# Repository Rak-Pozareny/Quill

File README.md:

# Quill
A love letter to the classic PDA, but reimagined.

Desktop and phone in one. A clean, all-transparent DORFic design that sits comfortably in your hand. Fully open source, top to bottom. What more could you ask for?
Meet Quill.

> **Status, November 2026.** Both boards are designed, pass every check run before manufacture, and are in
> production at JLCPCB; the compute module has arrived. Nothing has been powered
> on yet: every number on this page is a design value or the result of a check on the design files, not a measurement.

## What Quill is

A pocket computer in the spirit of the classic PDA: a square 4-inch screen above a thumb keyboard, running full desktop
Linux on an eight-core Rockchip RK3588S, with LTE, Wi-Fi 6, two cameras and a 5000 mAh battery. The electronics are two
custom boards: **Board A**, a 6-layer carrier for an Orange Pi CM5 compute module that holds everything except the
keyboard, and **Board B**, which connects a BlackBerry Q20 keyboard over USB.

| | |
|---|---|
| **Compute** | Orange Pi CM5: Rockchip RK3588S (4 x Cortex-A76 + 4 x Cortex-A55), 16 GB LPDDR4X, 32 GB eMMC |
| **Display** | 4.0" 720 x 720 IPS panel (DisplayModule DMKDI0400S0CA, ST7703), 4-lane MIPI DSI, capacitive touch |
| **Keyboard** | BlackBerry Q20 keyboard on Board B (RP2040), USB 2.0 to Board A |
| **Wireless** | Wi-Fi 6 2x2 + Bluetooth 5 (AMPAK AP6275P, PCIe 2.0 + UART); LTE Cat-6 (Quectel EM060K-GL, M.2, USB 3.0); nano-SIM |
| **Cameras** | rear: 4-lane MIPI CSI; front: 2-lane MIPI CSI |
| **Audio** | two I2S class-D amplifiers (MAX98357A) for stereo speakers, PDM MEMS microphone |
| **Ports** | USB-C (USB PD sink up to 12 V, charging and USB 2.0 data), 2 x USB-A behind a USB 2.0 hub, microSD |
| **Power** | 1S Li-ion 5000 mAh; buck-boost charger (BQ25713), fuel gauge (MAX17055), five DC-DC converters; battery path sized for 12 A |
| **Board A** | 95 x 65 mm, 6 layers, 1.2 mm, impedance-controlled; 432 footprints (379 parts placed by machine), 9,637 track segments, 1,841 vias |
| **Board B** | 74 x 53.1 mm, 2 layers, 2.0 mm; 68 parts |

## Architecture

The compute module plugs into Board A through three 100-pin board-to-board connectors (Hirose DF40). High-speed links
are drawn in red: DSI to the display, two CSI links to the cameras, PCIe to the Wi-Fi module, USB 3.0 to the LTE modem,
and USB 2.0 to the hub, the keyboard and the USB-C port.

**Power.** A USB-C PD controller (TPS25751, configured from an EEPROM so that it can boot from a flat battery) negotiates
5, 9 or 12 V and drives a narrow-VDC buck-boost charger. The system rail (VSYS, 3.0-4.5 V) feeds two boost converters
(5.03 V for the compute module, 5.1 V for USB, the keyboard and a camera), two buck-boost converters (3.7 V for the LTE
modem, 3.3 V for Wi-Fi, the hub and the cameras), the backlight driver and the audio amplifiers. With every load at its
maximum at once the battery supplies 33.6 W, 9.8 A at 3.5 V; the connector, protection circuit, battery FET and sense
resistors are all sized for 12 A. Realistic heavy use is about 13.9 W.

## Engineering highlights

### The boards are generated from code

The schematics, footprints, placement and routing are produced by about 16,000 lines of Python and C (`gen/`, `tools/`)
rather than drawn by hand, so every change is reproducible, can be reviewed as a diff, and is checked again on every
build. Board A's routing pipeline (`gen/route_a.py`, about six hours per full run) lays down the power pours and trunks,
routes the differential pairs as coupled lines with their impedance geometry (`gen/route_pairs.py`), fans out every
ground pad, routes the remaining connections with a negotiated-congestion (PathFinder) grid router whose core is written
in C (`gen/groute.c`), and tunes pair lengths with 45-degree bumps (`gen/route_tune.py`). How to run each step:
[docs/BUILDING.md](docs/BUILDING.md).

### Signal integrity on a 6-layer, 1.2 mm board

Layers 2 and 5 are ground planes, so each of the four signal layers has a ground plane next to it as its reference. Trace widths
and gaps come from JLCPCB's impedance calculator for its JLC06121H-3313A stack-up (Polar Si9000 models), and the
outer-layer ground pour keeps 0.30 mm from every controlled trace so that the microstrips behave as calculated:

| Class | Target | Outer layers, width / gap | Inner layers, width / gap | Used for |
|---|---|---|---|---|
| MIPI100 | 100 ohm differential | 0.110 / 0.155 mm | 0.100 / 0.200 mm | display and camera lanes, PCIe reference clocks |
| USB90 | 90 ohm differential | 0.120 / 0.110 mm | 0.100 / 0.110 mm | USB 2.0, USB 3.0 to the modem |
| PCIE85 | 85 ohm differential | 0.130 / 0.100 mm | 0.110 / 0.100 mm | PCIe to the Wi-Fi module |
| SE50 | 50 ohm single-ended | 0.155 mm | 0.125 mm | Wi-Fi antenna feeds, microSD |

Within each of the 31 differential pairs, the two traces match to 0.05 mm or better on 28; the other three are short
stubs, each explained in the decision log. Between lanes, the four display lanes are 55.08-55.22 mm long against a
55.12 mm clock. The camera links are not there yet: two of the rear camera's four lanes are 1.8-2.8 mm (12-20 ps) short
of their clock and the front camera's two lanes 2.8-2.9 mm (20 ps) long, against a +-1.0 mm allowance. Both will be
tested at full lane rate in bring-up ([length report](docs/opi/length_report.md)).

### Verification beyond the design-rule check

KiCad's design-rule check passes with 0 errors and 0 unconnected nets, the schematic and the board match exactly, and
the schematic passes its electrical-rule check. That was not enough, so the project added its own checks:

- **Review by the designer before every submission.** Before each set of Gerbers went to the manufacturer, Rak went
  through the design and the files. That review found, for example, that the part outlines on the silkscreen were drawn
  0.12 mm wide, under JLCPCB's 0.15 mm minimum (KiCad's default, missed by every automated check here; widened to
  0.15 mm for the next revision, D123), and produced a cleaner order package: a Gerber job file giving the fab every
  layer's function and order, and the impedance drawing and table set apart from the board layers with fabrication notes.
- **Engineering review at the manufacturer.** Every order's Gerber, drill, BOM and placement files went through
  JLCPCB's engineering review before production: their CAM engineers check the fabrication files for manufacturability,
  their SMT engineers check parts, land patterns and placement before assembly. Over three submissions of Board A they
  raised three problems (touching track ends, the Wi-Fi module's land pattern, copper too close for V-cut), all fixed and
  listed in the table below; the files now in production passed both reviews, as did Board B's. This is a
  manufacturability review, not a review of the circuit design: an independent design review is still an open item in
  [`REVIEW.md`](REVIEW.md).
- **Gerber-level connectivity** (`tools/gerber_check.py`). KiCad treats copper that merely touches as connected; a
  board house's CAM software does not. The exported Gerbers are read back as geometry and every track and via joint is
  measured the way the fab will see it.
- **Comparison with the manufacturer's production files** (`tools/jlc_prod_check/`). JLCPCB's CAM output for the
  order was parsed and compared with our copper layer by layer (geometric XOR), along with track widths, drill counts
  and any copper they added, before the order was confirmed.
- **Footprint audit** ([`docs/footprint_audit.md`](docs/footprint_audit.md)): each of the 24 footprints generated for
  the project checked against its datasheet drawing, down to which edge or centre each dimension line points to.
- **Parts**: every BOM line checked against JLCPCB's live catalogue (part number, manufacturer number, stock), and
  `tools/datasheets.py` confirms that every non-trivial part has its datasheet in [`datasheets/`](datasheets/README.md).

### What went wrong, and what changed because of it

| Date | What happened | Root cause | Response |
|---|---|---|---|
| 2026-10-30 | JLCPCB's CAM stopped the first order: track ends that only touched | KiCad's checks count touching copper as connected | 395 duplicate tracks removed, 153 joints bridged at full width (D110); the Gerber-level checker added (D116) |
| 2026-10-31 | Found in our own review: the outer ground pour ran 0.09 mm from controlled traces | a pour that close makes a microstrip coplanar, lowering its impedance | 0.30 mm keep-out around every controlled trace (D112) |
| 2026-11-06 | JLCPCB's assembly review: the Wi-Fi module's 50 pads sat 0.56 mm too far in | a datasheet dimension measured between pad centres had been read as between pad edges | footprint corrected, board re-routed (D114); every other footprint audited for the same misreading (D115) |
| 2026-11-10 | The display maker's drawing put pin 1 of both panel cables at the other end | the pin direction had been assumed and was marked UNVERIFIED | connectors mirrored and the whole board routed again (D118) |
| 2026-11-15 | JLCPCB: copper too close to the edge rails for V-cut separation | 0.25 mm edge clearance, fine for routed edges, too small for V-cut | rails joined by mouse-bite tabs instead; 0.4 mm clearance for the next revision (D122) |

### Every decision is written down

[`docs/DECISIONS.md`](docs/DECISIONS.md) records 122 design decisions and 22 answered design questions, each with the
choice, the alternatives and the reason, and the sources behind it. Anything not confirmed from a primary source (a
datasheet, a drawing, a measurement) is marked **UNVERIFIED** until it is.

<p align="center"><sub>Left: Board A, bottom side (LTE modem, Wi-Fi module, power stages). Right: Board B, the keyboard board.</sub></p>

## Repository

| Path | Contents |
|---|---|
| [`gen/`](gen/) | generators: schematics, footprints, placement, routing (`route_*.py`, `groute.c`), length tuning |
| [`hw/`](hw/) | the KiCad 10 projects for Board A (`board_a/`) and Board B (`board_b/`), produced by `gen/` |
| [`fab/`](fab/) | the manufacturing packages: Gerbers, drill files, BOM, placement, stack-up, impedance drawing, `ORDER.md` |
| [`tools/`](tools/) | checks and reports: Gerber connectivity, production-file comparison, BOM, impedance, datasheets, images |
| [`docs/`](docs/README.md) | design reports, decision log, review, status, enclosure; index in [`docs/README.md`](docs/README.md) |
| [`datasheets/`](datasheets/README.md) | datasheets, drawings and reference designs the design rests on, with an index |
| [`software/`](software/) | Linux device tree for the Orange Pi images (written, not yet tested on hardware) |
| [`REVIEW.md`](REVIEW.md) | the pre-manufacture review: open points, assumptions, what an experienced engineer should check |

## Roadmap

- [x] Requirements, architecture, pin and power budgets
- [x] Schematics, placement, routing and manufacturing files for both boards
- [x] Board A redesigned for the Orange Pi CM5 when the original compute module (Radxa CM5) could not be bought
- [x] Board A rev A ordered: 6 layers, impedance-controlled, assembled by JLCPCB
- [x] Board B ordered
- [ ] Bring-up: power rails, USB PD and charger configuration, first boot, display, cameras, Wi-Fi, LTE
- [ ] Measurements: converter efficiency, battery life, thermals, signal quality on the high-speed links
- [ ] Linux device tree and drivers validated on the hardware
- [ ] Enclosure: a transparent swivel case (concept in [`docs/enclosure/`](docs/enclosure/))
- [ ] Rev B with what bring-up teaches
- [ ] A write-up of the whole project as a paper

## How Quill is made

Quill is designed by Rak Pozareny with Claude, an AI model made by Anthropic, used through Claude Code. Rak defined the
device and its requirements, made the calls at each decision point, sourced the modules and parts, reviewed the design
and its Gerber files personally before every submission to the manufacturer, and handles the manufacturers and
suppliers; the hardware will be assembled and tested by hand. Claude wrote the generator and checking code, produced
the schematics and layout with it, and wrote most of the documentation. Commits made with Claude carry a
`Co-Authored-By: Claude` line.

## Licences

Everything here is under the MIT licence ([`LICENSE`](LICENSE)), except:

- **Board B** (`hw/board_b/`, `fab/board_b/`, and `gen/build_b.py`, `gen/pcb_b.py`, `gen/route_b.py`, which build it):
  its keyboard connector placement and outline are derived from Solder Party's
  [BBQ20KBD](https://github.com/solderparty/bbq20kbd_hw), so it is released under the CERN Open Hardware Licence v1.2
  ([`hw/board_b/LICENSE.md`](hw/board_b/LICENSE.md)). The recommended firmware,
  [i2c_puppet](https://github.com/solderparty/i2c_puppet), is MIT-licensed.
- **[`datasheets/`](datasheets/README.md)**: other companies' documents (datasheets, drawings, reference schematics),
  copyright their makers, kept here for reference and not covered by the MIT licence. The BBQ20KBD files there are
  CERN-OHL v1.2 (licence beside them).

## Acknowledgements

Solder Party's BBQ20KBD and i2c_puppet, which Board B and its firmware build on; Orange Pi, Radxa and Khadas, whose
published schematics and drawings served as reference designs; and the open-source KiCad project.

The renders use the parts' 3D models from the **JLCEDA / EasyEDA Official Library** ([lceda.cn](https://lceda.cn/),
[easyeda.com](https://easyeda.com)), fitted onto this design's footprints by `tools/media.py`; the compute module, the
LTE card, the USB-A ports and the battery connector are modelled from their drawings and a photo of the module.

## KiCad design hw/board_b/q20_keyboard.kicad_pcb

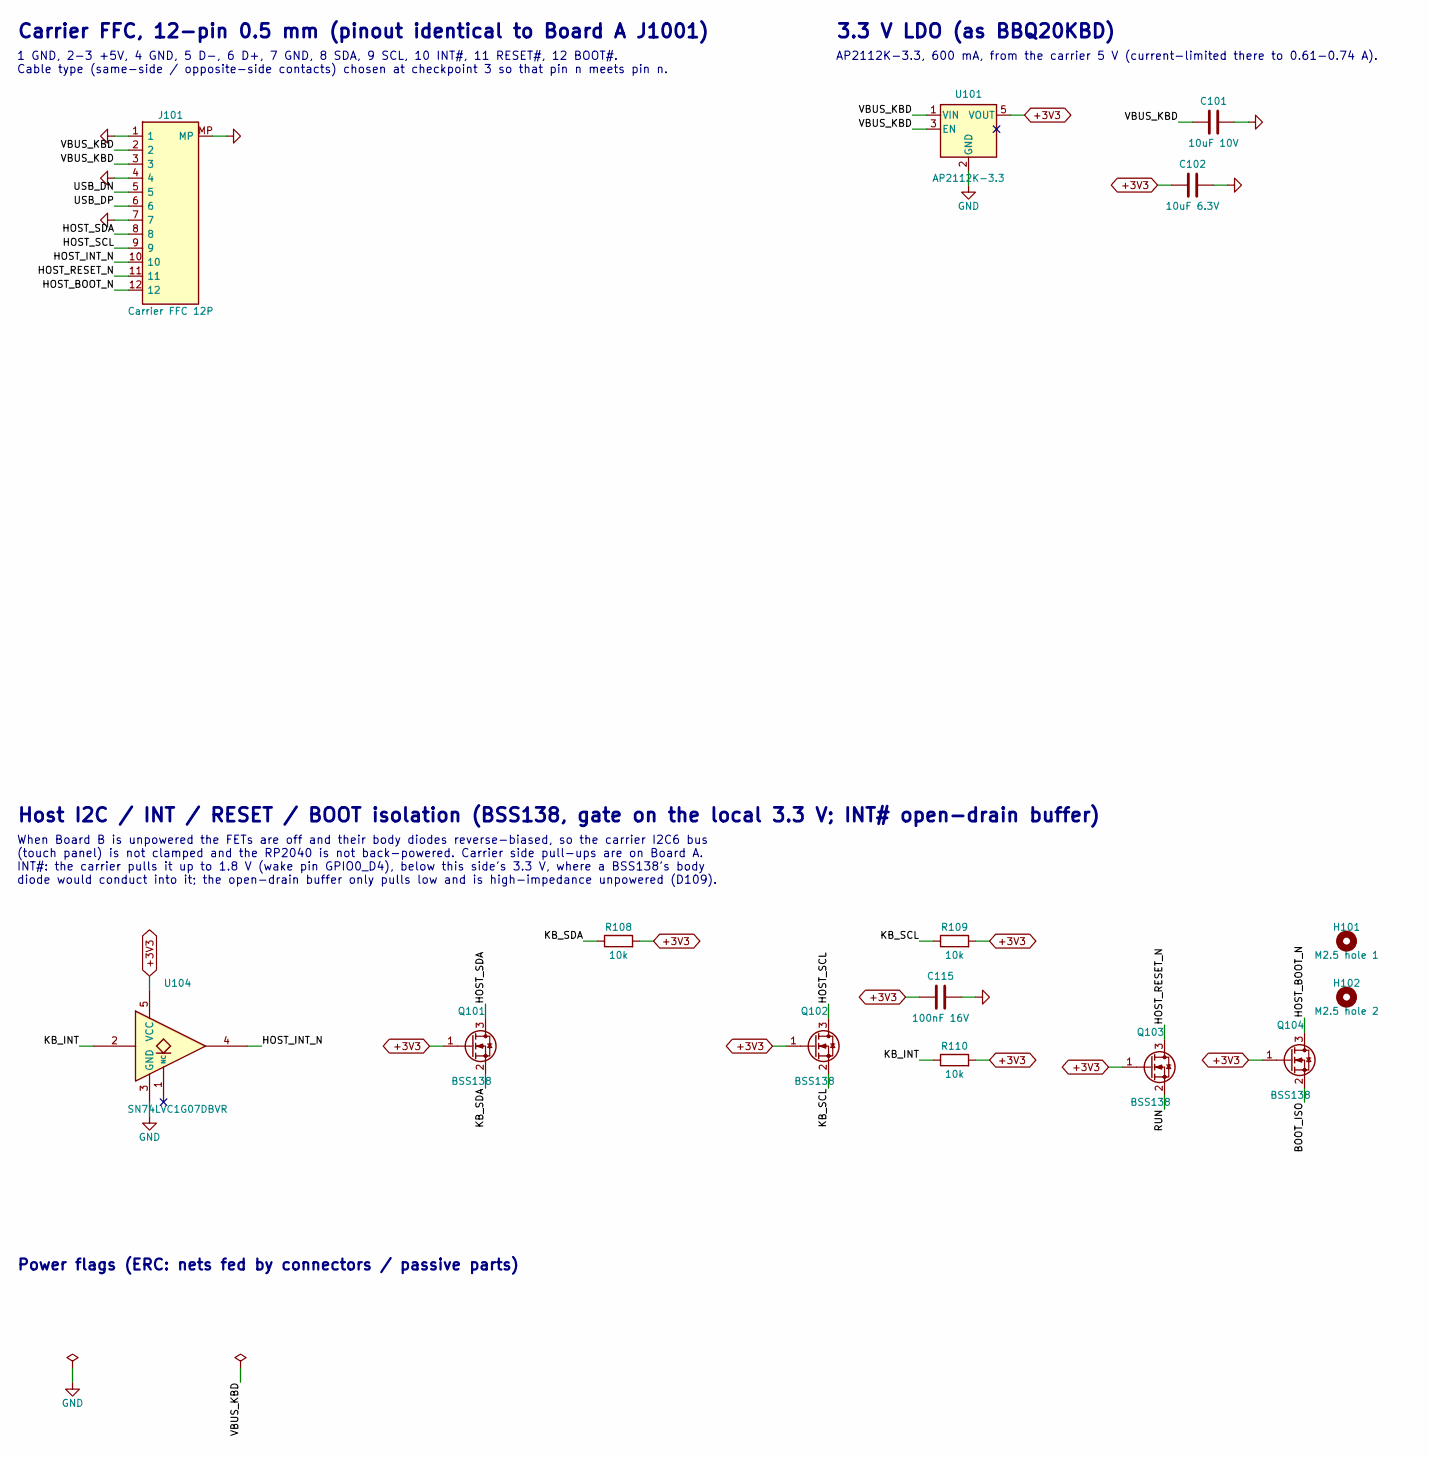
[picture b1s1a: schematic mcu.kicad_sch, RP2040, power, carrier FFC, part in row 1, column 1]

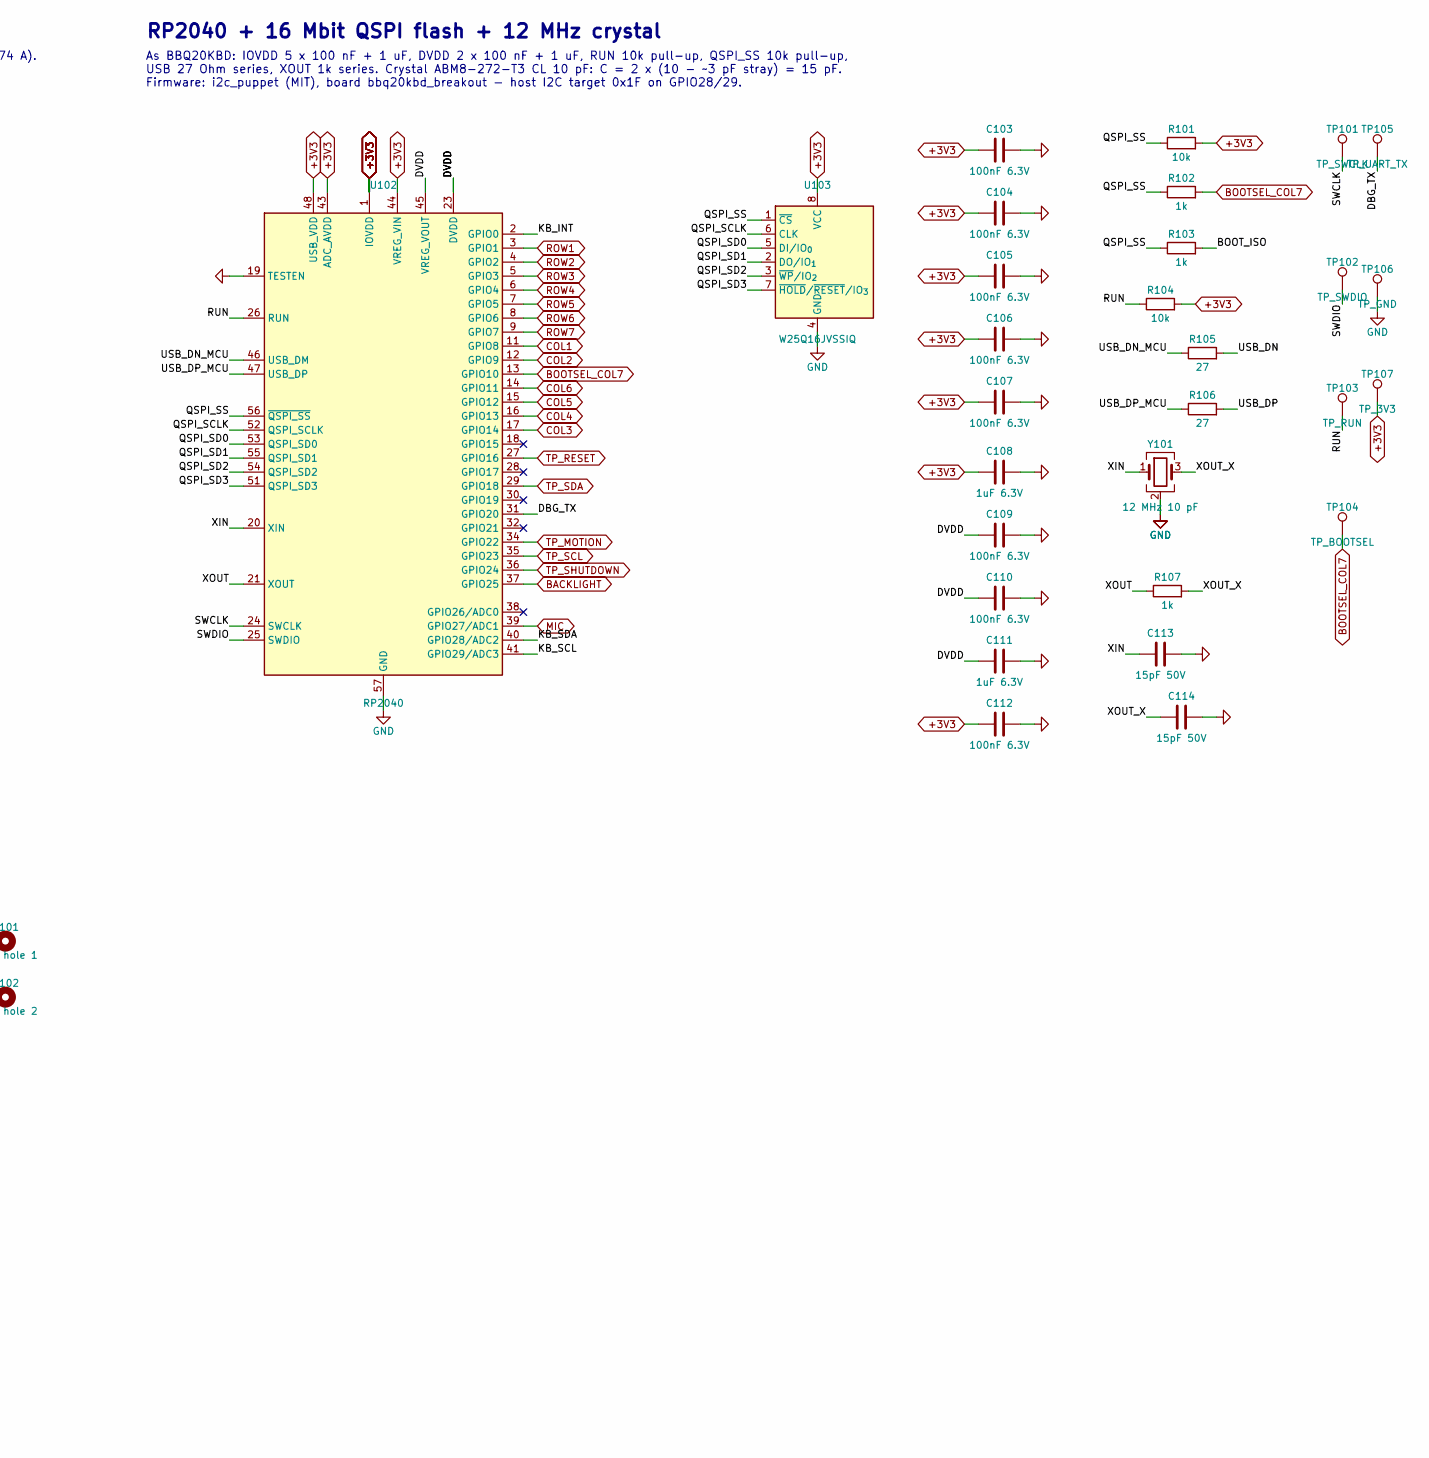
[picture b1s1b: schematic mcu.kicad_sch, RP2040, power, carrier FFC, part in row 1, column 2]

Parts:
C101: 10uF 10V; C_0603_1608Metric; MPN CL10A106KP8NNNC; LCSC C19702
C102: 10uF 6.3V; C_0603_1608Metric; MPN CL10A106KP8NNNC; LCSC C19702
C103, C104, C105, C106, C107, C109, C110, C112: 100nF 6.3V; C_0402_1005Metric; MPN CL05B104KO5NNNC; LCSC C1525
C108, C111: 1uF 6.3V; C_0402_1005Metric; MPN CL05A105KA5NQNC; LCSC C52923
C113, C114: 15pF 50V; C_0402_1005Metric; MPN 0402CG150J500NT; LCSC C1548
C115: 100nF 16V; C_0402_1005Metric; MPN CL05B104KO5NNNC; LCSC C1525
H101: M2.5 hole 1; MountingHole_2.7mm_M2.5
H102: M2.5 hole 2; MountingHole_2.7mm_M2.5
J101: Carrier FFC 12P; FPC_0.5mm_12P_BXCONN_FC-05A12P11H20; MPN FC-05A12P11H20; LCSC C23398836
Q101, Q102, Q103, Q104: BSS138; SOT-23; MPN BSS138-7-F; LCSC C40912
R101, R104, R108, R109, R110: 10k; R_0402_1005Metric; MPN 0402WGF1002TCE; LCSC C25744
R102, R103, R107: 1k; R_0402_1005Metric; MPN 0402WGF1001TCE; LCSC C11702
R105, R106: 27; R_0402_1005Metric; MPN FRC0402F27R0TS; LCSC C2909343
TP101: TP_SWCLK; TestPoint_Pad_D1.5mm
TP102: TP_SWDIO; TestPoint_Pad_D1.5mm
TP103: TP_RUN; TestPoint_Pad_D1.5mm
TP104: TP_BOOTSEL; TestPoint_Pad_D1.5mm
TP105: TP_UART_TX; TestPoint_Pad_D1.5mm
TP106: TP_GND; TestPoint_Pad_D1.5mm
TP107: TP_3V3; TestPoint_Pad_D1.5mm
U101: AP2112K-3.3; SOT-23-5; MPN AP2112K-3.3TRG1; LCSC C51118
U102: RP2040; QFN-56-1EP_7x7mm_P0.4mm_EP3.2x3.2mm; MPN RP2040; LCSC C2040
U103: W25Q16JVSSIQ; SOIC-8_5.3x5.3mm_P1.27mm; MPN W25Q16JVSSIQ; LCSC C131025
U104: SN74LVC1G07DBVR; SOT-23-5; MPN SN74LVC1G07DBVR; LCSC C7829
Y101: 12 MHz 10 pF; Crystal_SMD_3225-4Pin_3.2x2.5mm; MPN ABM8-272-T3; LCSC C20625731

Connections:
+3V3: C102.1, C103.1, C104.1, C105.1, C106.1, C107.1, C108.1, C112.1, C115.1, Q101.1 (G), Q102.1 (G), Q103.1 (G), Q104.1 (G), R101.2, R104.2, R108.2, R109.2, R110.2, TP107.1, U101.5 (VOUT), U102.1 (IOVDD), U102.10 (IOVDD), U102.22 (IOVDD), U102.33 (IOVDD), U102.42 (IOVDD), U102.43 (ADC_AVDD), U102.44 (VREG_VIN), U102.48 (USB_VDD), U102.49 (IOVDD), U103.8 (VCC), U104.5 (VCC); also elsewhere on the board
/RP2040, power, carrier FFC/BOOT_ISO: Q104.2 (S), R103.2
/RP2040, power, carrier FFC/DBG_TX: TP105.1, U102.31 (GPIO20)
/RP2040, power, carrier FFC/DVDD: C109.1, C110.1, C111.1, U102.23 (DVDD), U102.45 (VREG_VOUT), U102.50 (DVDD)
/RP2040, power, carrier FFC/HOST_BOOT_N: J101.12, Q104.3 (D)
/RP2040, power, carrier FFC/HOST_INT_N: J101.10, U104.4
/RP2040, power, carrier FFC/HOST_RESET_N: J101.11, Q103.3 (D)
/RP2040, power, carrier FFC/HOST_SCL: J101.9, Q102.3 (D)
/RP2040, power, carrier FFC/HOST_SDA: J101.8, Q101.3 (D)
/RP2040, power, carrier FFC/KB_INT: R110.1, U102.2 (GPIO0), U104.2
/RP2040, power, carrier FFC/KB_SCL: Q102.2 (S), R109.1, U102.41 (GPIO29/ADC3)
/RP2040, power, carrier FFC/KB_SDA: Q101.2 (S), R108.1, U102.40 (GPIO28/ADC2)
/RP2040, power, carrier FFC/QSPI_SCLK: U102.52 (QSPI_SCLK), U103.6 (CLK)
/RP2040, power, carrier FFC/QSPI_SD0: U102.53 (QSPI_SD0), U103.5 (DI/IO_{0})
/RP2040, power, carrier FFC/QSPI_SD1: U102.55 (QSPI_SD1), U103.2 (DO/IO_{1})
/RP2040, power, carrier FFC/QSPI_SD2: U102.54 (QSPI_SD2), U103.3 (~WP/IO_{2})
/RP2040, power, carrier FFC/QSPI_SD3: U102.51 (QSPI_SD3), U103.7 (~HOLD/~RESET/IO_{3})
/RP2040, power, carrier FFC/QSPI_SS: R101.1, R102.1, R103.1, U102.56 (~QSPI_SS), U103.1 (~CS)
/RP2040, power, carrier FFC/RUN: Q103.2 (S), R104.1, TP103.1, U102.26 (RUN)
/RP2040, power, carrier FFC/SWCLK: TP101.1, U102.24 (SWCLK)
/RP2040, power, carrier FFC/SWDIO: TP102.1, U102.25 (SWDIO)
/RP2040, power, carrier FFC/USB_DN: J101.5, R105.2
/RP2040, power, carrier FFC/USB_DN_MCU: R105.1, U102.46 (USB_DM)
/RP2040, power, carrier FFC/USB_DP: J101.6, R106.2
/RP2040, power, carrier FFC/USB_DP_MCU: R106.1, U102.47 (USB_DP)
/RP2040, power, carrier FFC/VBUS_KBD: C101.1, J101.2, J101.3, U101.1 (VIN), U101.3 (EN)
/RP2040, power, carrier FFC/XIN: C113.1, U102.20 (XIN), Y101.1
/RP2040, power, carrier FFC/XOUT: R107.1, U102.21 (XOUT)
/RP2040, power, carrier FFC/XOUT_X: C114.1, R107.2, Y101.3
BACKLIGHT: U102.37 (GPIO25); also elsewhere on the board
BOOTSEL_COL7: R102.2, TP104.1, U102.13 (GPIO10); also elsewhere on the board
COL1: U102.11 (GPIO8); also elsewhere on the board
COL2: U102.12 (GPIO9); also elsewhere on the board
COL3: U102.17 (GPIO14); also elsewhere on the board
COL4: U102.16 (GPIO13); also elsewhere on the board
COL5: U102.15 (GPIO12); also elsewhere on the board
COL6: U102.14 (GPIO11); also elsewhere on the board
GND: C101.2, C102.2, C103.2, C104.2, C105.2, C106.2, C107.2, C108.2, C109.2, C110.2, C111.2, C112.2, C113.2, C114.2, C115.2, J101.1, J101.4, J101.7, J101.MP, TP106.1, U101.2 (GND), U102.19 (TESTEN), U102.57 (GND), U103.4 (GND), U104.3 (GND), Y101.2 (G), Y101.4 (G); also elsewhere on the board
MIC: U102.39 (GPIO27/ADC1); also elsewhere on the board
ROW1: U102.3 (GPIO1); also elsewhere on the board
ROW2: U102.4 (GPIO2); also elsewhere on the board
ROW3: U102.5 (GPIO3); also elsewhere on the board
ROW4: U102.6 (GPIO4); also elsewhere on the board
ROW5: U102.7 (GPIO5); also elsewhere on the board
ROW6: U102.8 (GPIO6); also elsewhere on the board
ROW7: U102.9 (GPIO7); also elsewhere on the board
TP_MOTION: U102.34 (GPIO22); also elsewhere on the board
TP_RESET: U102.27 (GPIO16); also elsewhere on the board
TP_SCL: U102.35 (GPIO23); also elsewhere on the board
TP_SDA: U102.29 (GPIO18); also elsewhere on the board
TP_SHUTDOWN: U102.36 (GPIO24); also elsewhere on the board

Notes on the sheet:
Carrier FFC, 12-pin 0.5 mm (pinout identical to Board A J1001)
1 GND, 2-3 +5V, 4 GND, 5 D-, 6 D+, 7 GND, 8 SDA, 9 SCL, 10 INT#, 11 RESET#, 12 BOOT#. Cable type (same-side / opposite-side contacts) chosen at checkpoint 3 so that pin n meets pin n.
3.3 V LDO (as BBQ20KBD)
AP2112K-3.3, 600 mA, from the carrier 5 V (current-limited there to 0.61-0.74 A).
RP2040 + 16 Mbit QSPI flash + 12 MHz crystal
As BBQ20KBD: IOVDD 5 x 100 nF + 1 uF, DVDD 2 x 100 nF + 1 uF, RUN 10k pull-up, QSPI_SS 10k pull-up, USB 27 Ohm series, XOUT 1k series. Crystal ABM8-272-T3 CL 10 pF: C = 2 x (10 - ~3 pF stray) = 15 pF. Firmware: i2c_puppet (MIT), board bbq20kbd_breakout - host I2C target 0x1F on GPIO28/29.
Host I2C / INT / RESET / BOOT isolation (BSS138, gate on the local 3.3 V; INT# open-drain buffer)
When Board B is unpowered the FETs are off and their body diodes reverse-biased, so the carrier I2C6 bus (touch panel) is not clamped and the RP2040 is not back-powered. Carrier side pull-ups are on Board A. INT#: the carrier pulls it up to 1.8 V (wake pin GPIO0_D4), below this side's 3.3 V, where 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
Power flags (ERC: nets fed by connectors / passive parts)

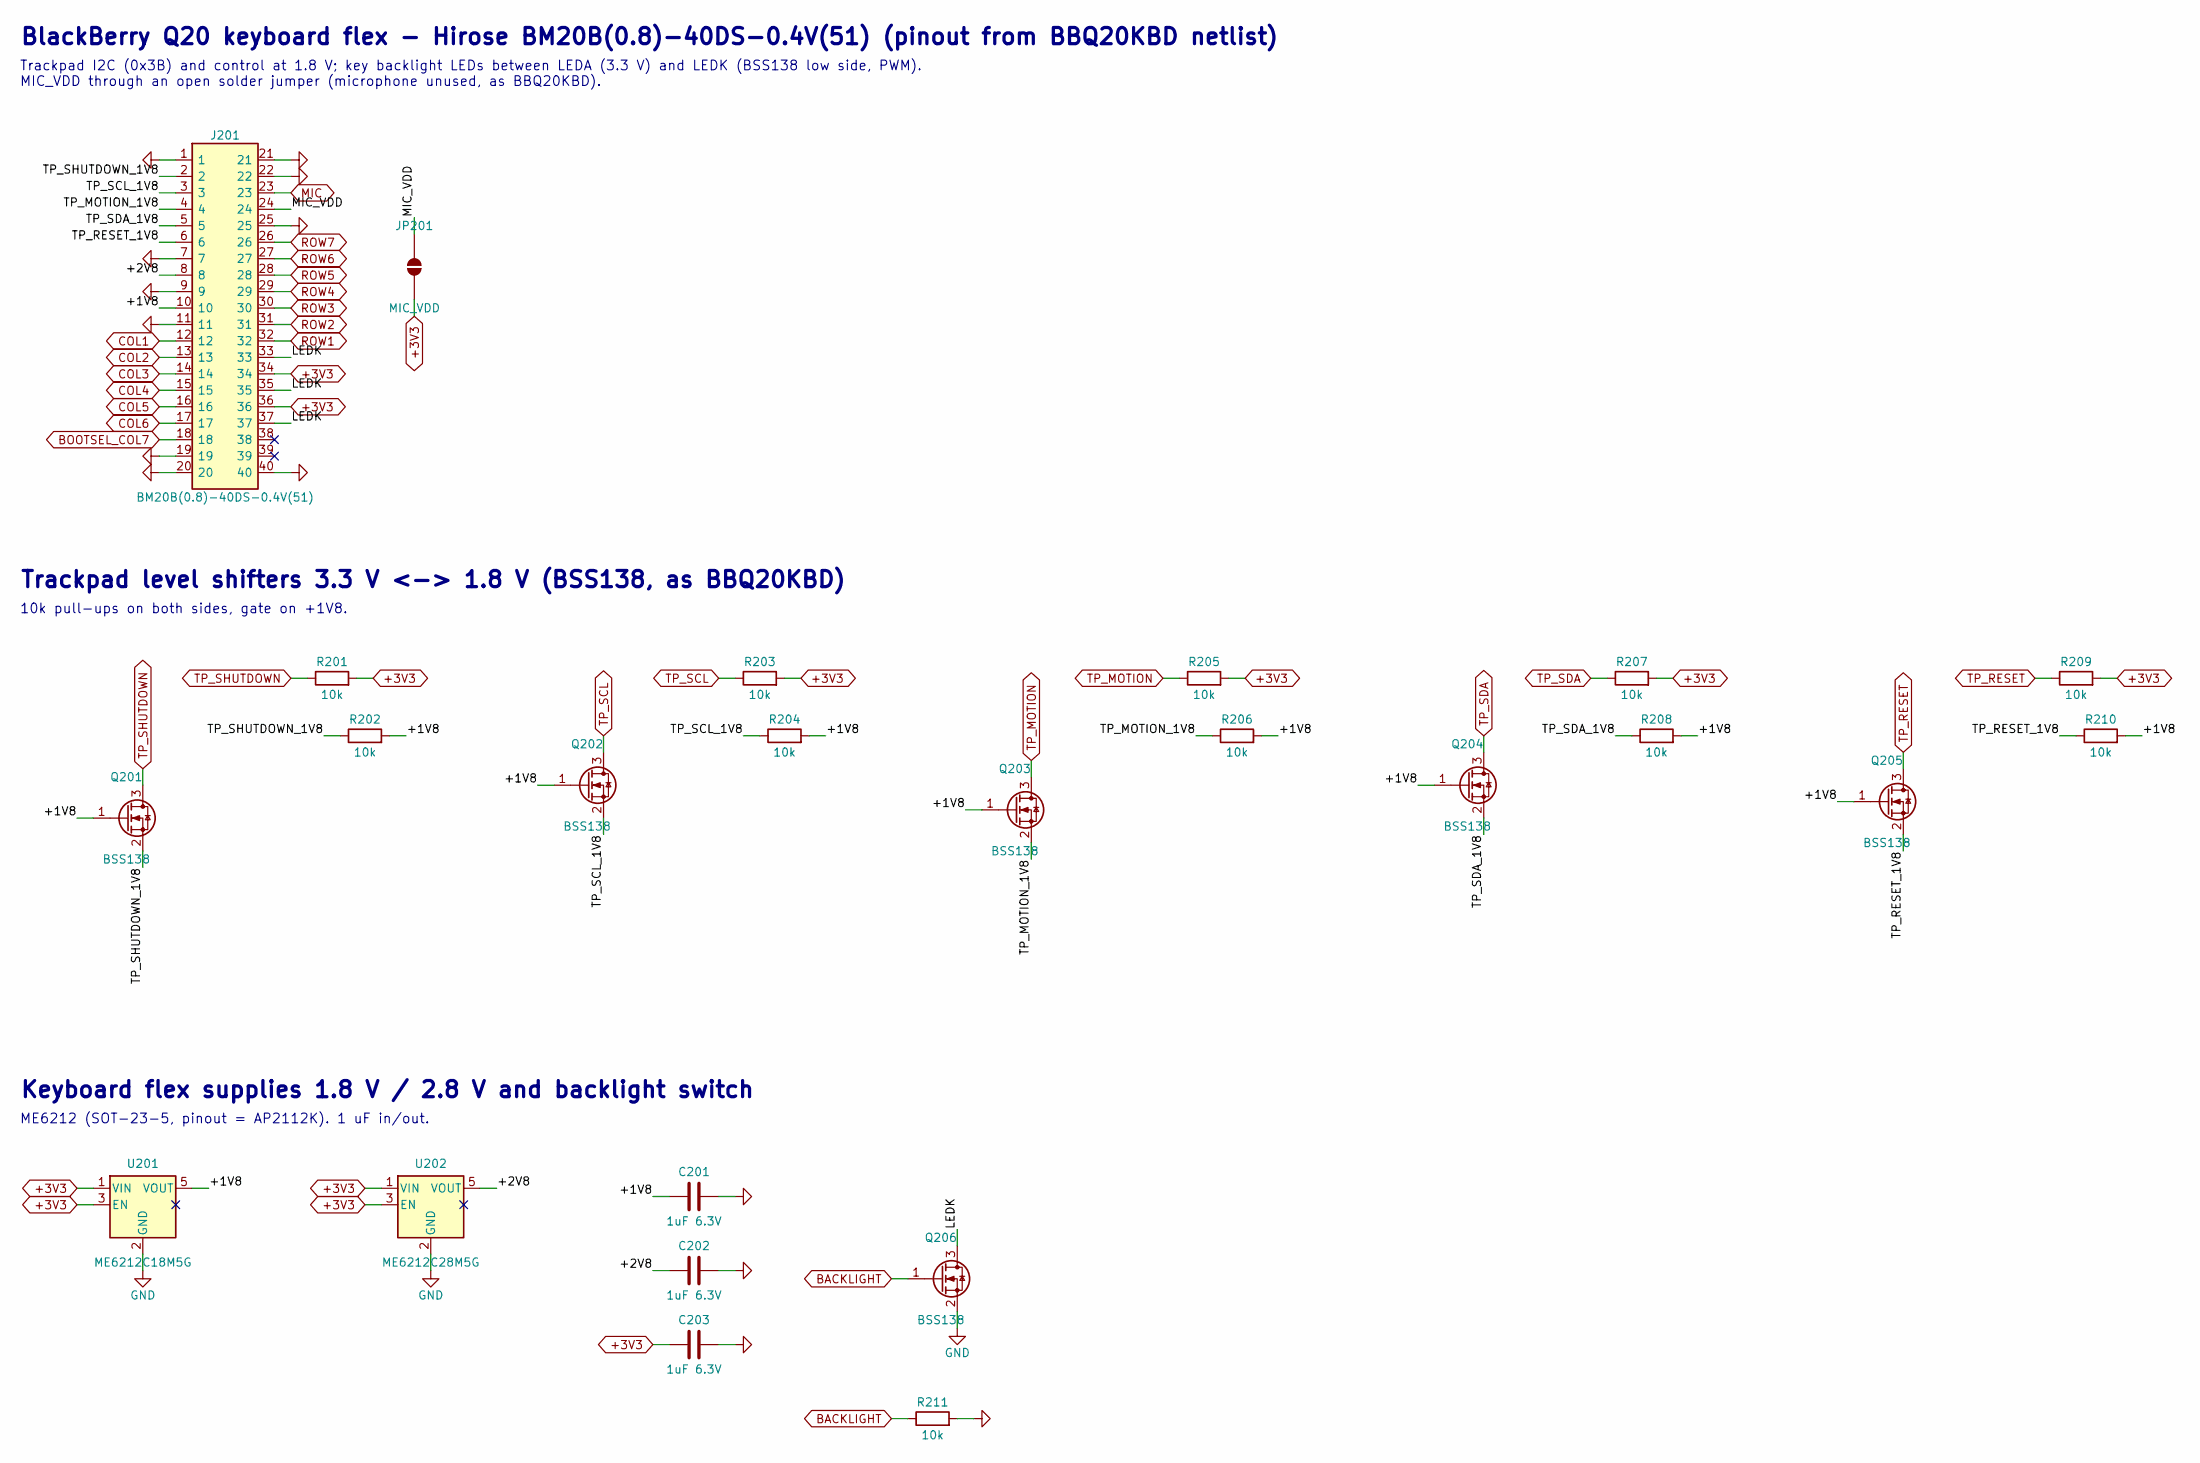
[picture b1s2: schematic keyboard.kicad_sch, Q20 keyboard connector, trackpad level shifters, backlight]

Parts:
C201, C202, C203: 1uF 6.3V; C_0402_1005Metric; MPN CL05A105KA5NQNC; LCSC C52923
J201: BM20B(0.8)-40DS-0.4V(51); Hirose_BM20B_0.8_-40DS-0.4V; MPN BM20B(0.8)-40DS-0.4V(51); LCSC C424543
JP201: MIC_VDD; SolderJumper-2_P1.3mm_Open_RoundedPad1.0x1.5mm
Q201, Q202, Q203, Q204, Q205, Q206: BSS138; SOT-23; MPN BSS138-7-F; LCSC C40912
R201, R202, R203, R204, R205, R206, R207, R208, R209, R210, R211: 10k; R_0402_1005Metric; MPN 0402WGF1002TCE; LCSC C25744
U201: ME6212C18M5G; SOT-23-5; MPN ME6212C18M5G; LCSC C236669
U202: ME6212C28M5G; SOT-23-5; MPN ME6212C28M5G; LCSC C427596

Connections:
+3V3: C203.1, J201.34, J201.36, JP201.1 (A), R201.2, R203.2, R205.2, R207.2, R209.2, U201.1 (VIN), U201.3 (EN), U202.1 (VIN), U202.3 (EN); also elsewhere on the board
/Q20 keyboard connector, trackpad level shifters, backlight/+1V8: C201.1, J201.10, Q201.1 (G), Q202.1 (G), Q203.1 (G), Q204.1 (G), Q205.1 (G), R202.2, R204.2, R206.2, R208.2, R210.2, U201.5 (VOUT)
/Q20 keyboard connector, trackpad level shifters, backlight/+2V8: C202.1, J201.8, U202.5 (VOUT)
/Q20 keyboard connector, trackpad level shifters, backlight/LEDK: J201.33, J201.35, J201.37, Q206.3 (D)
/Q20 keyboard connector, trackpad level shifters, backlight/MIC_VDD: J201.24, JP201.2 (B)
/Q20 keyboard connector, trackpad level shifters, backlight/TP_MOTION_1V8: J201.4, Q203.2 (S), R206.1
/Q20 keyboard connector, trackpad level shifters, backlight/TP_RESET_1V8: J201.6, Q205.2 (S), R210.1
/Q20 keyboard connector, trackpad level shifters, backlight/TP_SCL_1V8: J201.3, Q202.2 (S), R204.1
/Q20 keyboard connector, trackpad level shifters, backlight/TP_SDA_1V8: J201.5, Q204.2 (S), R208.1
/Q20 keyboard connector, trackpad level shifters, backlight/TP_SHUTDOWN_1V8: J201.2, Q201.2 (S), R202.1
BACKLIGHT: Q206.1 (G), R211.1; also elsewhere on the board
BOOTSEL_COL7: J201.18; also elsewhere on the board
COL1: J201.12; also elsewhere on the board
COL2: J201.13; also elsewhere on the board
COL3: J201.14; also elsewhere on the board
COL4: J201.15; also elsewhere on the board
COL5: J201.16; also elsewhere on the board
COL6: J201.17; also elsewhere on the board
GND: C201.2, C202.2, C203.2, J201.1, J201.7, J201.9, J201.11, J201.19, J201.20, J201.21, J201.22, J201.25, J201.40, Q206.2 (S), R211.2, U201.2 (GND), U202.2 (GND); also elsewhere on the board
MIC: J201.23; also elsewhere on the board
ROW1: J201.32; also elsewhere on the board
ROW2: J201.31; also elsewhere on the board
ROW3: J201.30; also elsewhere on the board
ROW4: J201.29; also elsewhere on the board
ROW5: J201.28; also elsewhere on the board
ROW6: J201.27; also elsewhere on the board
ROW7: J201.26; also elsewhere on the board
TP_MOTION: Q203.3 (D), R205.1; also elsewhere on the board
TP_RESET: Q205.3 (D), R209.1; also elsewhere on the board
TP_SCL: Q202.3 (D), R203.1; also elsewhere on the board
TP_SDA: Q204.3 (D), R207.1; also elsewhere on the board
TP_SHUTDOWN: Q201.3 (D), R201.1; also elsewhere on the board

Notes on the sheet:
BlackBerry Q20 keyboard flex - Hirose BM20B(0.8)-40DS-0.4V(51) (pinout from BBQ20KBD netlist)
Trackpad I2C (0x3B) and control at 1.8 V; key backlight LEDs between LEDA (3.3 V) and LEDK (BSS138 low side, PWM). MIC_VDD through an open solder jumper (microphone unused, as BBQ20KBD).
Trackpad level shifters 3.3 V <-> 1.8 V (BSS138, as BBQ20KBD)
10k pull-ups on both sides, gate on +1V8.
Keyboard flex supplies 1.8 V / 2.8 V and backlight switch
ME6212 (SOT-23-5, pinout = AP2112K). 1 uF in/out.

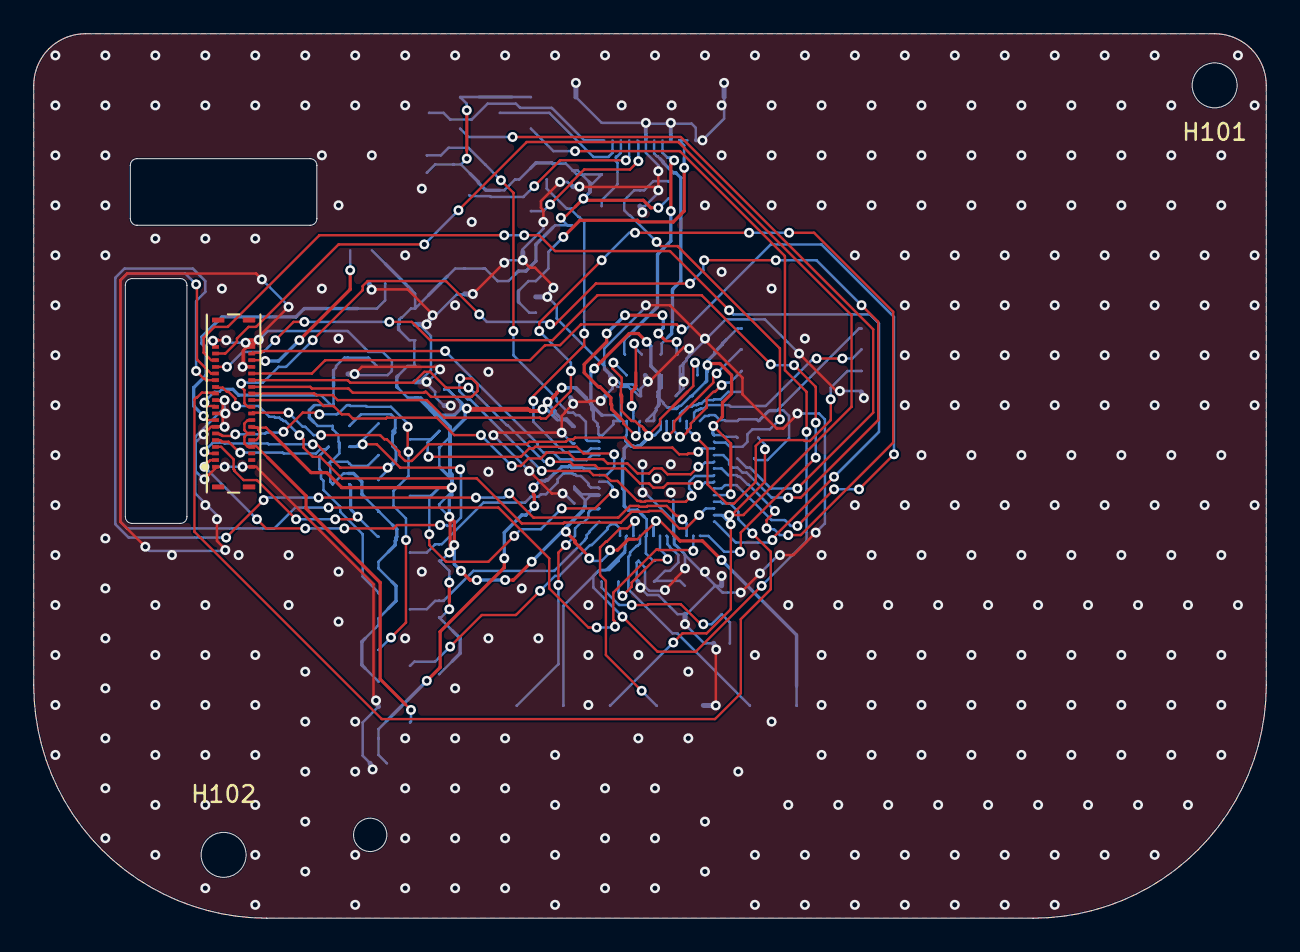
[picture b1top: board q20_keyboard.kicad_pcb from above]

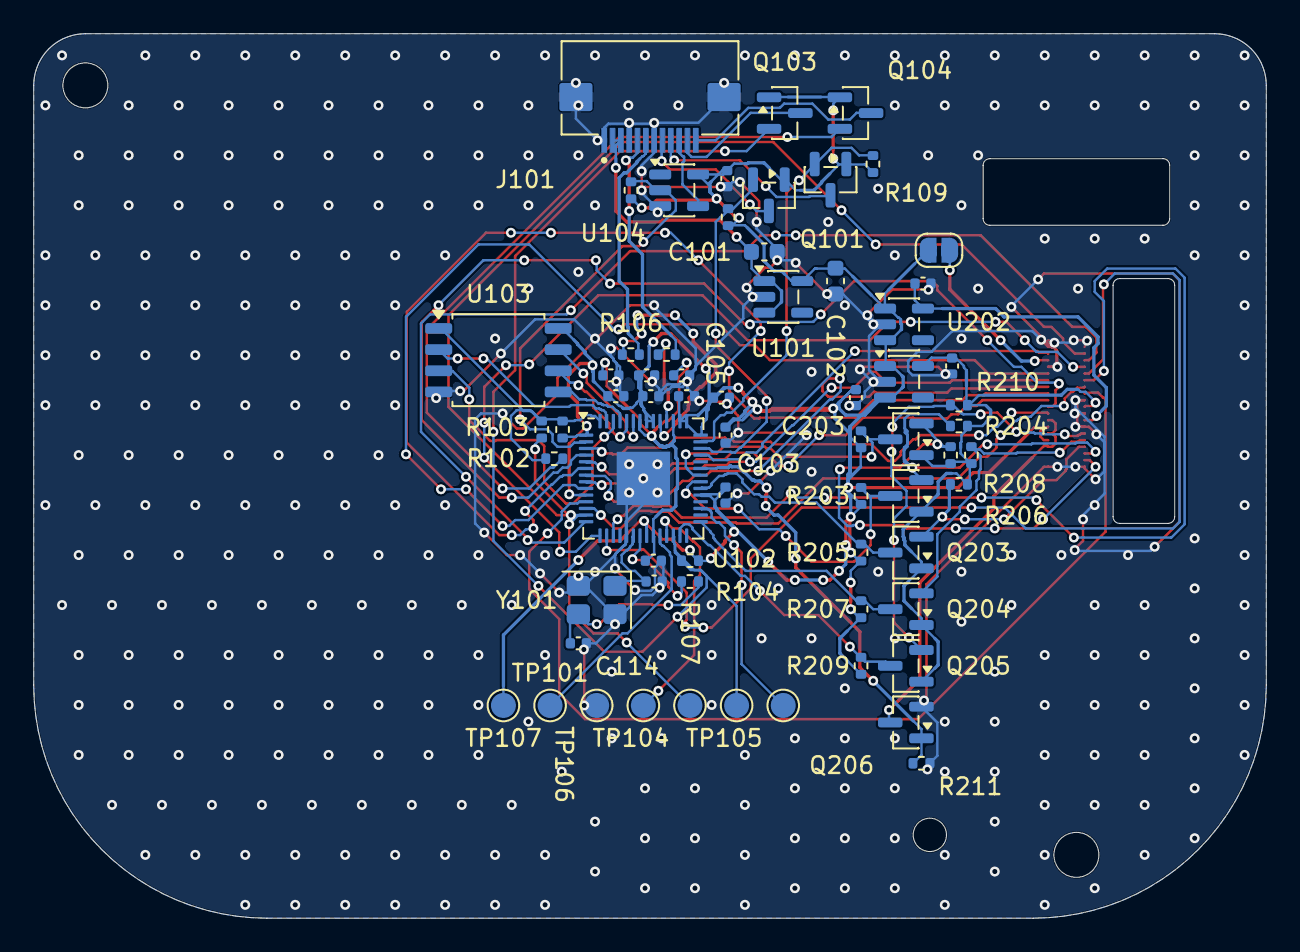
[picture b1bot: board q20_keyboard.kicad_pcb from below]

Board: 2 copper layers, 74.0 x 53.1 mm, 68 parts (65 on the bottom side), 60 nets.

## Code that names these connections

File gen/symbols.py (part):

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        sub[1] = Q(str(sub[1]).replace('TPS25751D', 'TPS25751D', 1))
        for pin in find_all(sub, 'pin'):
            name = str([x for x in pin if isinstance(x, list) and x[0] == 'name'][0][1])
            if name in ('GPIO0', 'GPIO1', 'GPIO2', 'GPIO3', 'GPIO6', 'GPIO7', 'GPIO11'):
                pin[1] = 'passive'
            if name == '~{I2Ct_IRQ}':
                pin[1] = 'open_collector'
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
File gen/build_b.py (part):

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    g = sb.group('RP2040 + 16 Mbit QSPI flash + 12 MHz crystal',
                 'As BBQ20KBD: IOVDD 5 x 100 nF + 1 uF, DVDD 2 x 100 nF + 1 uF, RUN 10k pull-up, QSPI_SS 10k pull-up,\n'
                 'USB 27 Ohm series, XOUT 1k series. Crystal ABM8-272-T3 CL 10 pF: C = 2 x (10 - ~3 pF stray) = 15 pF.\n'
                 'Firmware: i2c_puppet (MIT), board bbq20kbd_breakout - host I2C target 0x1F on GPIO28/29.')
    pin = {'1': '+3V3', '43': '+3V3', '44': '+3V3', '48': '+3V3', '23': 'DVDD', '45': 'DVDD', '57': 'GND', '19': 'GND',
           '2': 'KB_INT', '3': 'ROW1', '4': 'ROW2', '5': 'ROW3', '6': 'ROW4', '7': 'ROW5', '8': 'ROW6', '9': 'ROW7',
           '11': 'COL1', '12': 'COL2', '17': 'COL3', '16': 'COL4', '15': 'COL5', '14': 'COL6', '13': 'BOOTSEL_COL7',
           '18': None, '27': 'TP_RESET', '28': None, '29': 'TP_SDA', '30': None, '31': 'DBG_TX', '32': None,
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        g.R('10k', sig, '+3V3')
        g.R('10k', f'{sig}_1V8', '+1V8')

    g = sb.group('Keyboard flex supplies 1.8 V / 2.8 V and backlight switch', 'ME6212 (SOT-23-5, pinout = AP2112K). 1 uF in/out.')
    P(g, 'ME6212_18', 'Regulator_Linear:AP2112K-3.3', 'ME6212C18M5G', {'1': '+3V3', '2': 'GND', '3': '+3V3', '4': None,
                                                                     '5': '+1V8'})
    g.C('1uF', '+1V8')
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                                                                     '5': '+2V8'})
    g.C('1uF', '+2V8')
    g.C('1uF', '+3V3')
    bss138(g, 'LEDK', 'BACKLIGHT', 'GND', note='backlight PWM (GPIO25)')
    g.R('10k', 'BACKLIGHT', 'GND')
    return d

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
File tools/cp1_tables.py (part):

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add('B', '103,105', 'TYPEC0_OTG_DM/DP', 'USB20 OTG0', 'USB PHY', 'USB-C data (device default, Maskrom)', 'USB-C receptacle D-/D+ via 2.2R + CMC + ESD', 'OTG0 is the Maskrom/download port', 'PX U13-B; CM5 p12; IO p18')
add('C', '97', 'TYPEC0_OTG_VBUSDET', 'TYPEC0_USB20_VBUSDET', '3.3 V (4.7k pull-up on module)', 'left at module default', '- (option: NMOS pull-down when VBUS absent)', 'Same as Radxa IO board (pin NC)', 'PX J1; CM5 p12; IO p17')
add('C', '63,65', 'USB20_HOST0_DP/DM', 'USB2 HOST0', 'USB PHY', 'USB hub upstream', 'USB2514B upstream port', 'Same port Radxa uses for its FE1.1s hub', 'PX J1; IO p12')
add('C', '45,47', 'USB20_HOST1_DP/DM', 'USB2 HOST1', 'USB PHY', 'LTE modem USB 2.0 (direct)', 'M.2 Key-B pins 7/9 (USB_DP/USB_DM)', 'USB 2.0 half of the modem USB 3.0 link (same pairing as Radxa IO-board USB 3.0 port)', 'PX J1; IO p13; EM060K HD V1.1 s.4.1')
add('C', '51,53', 'USB30_2_SSTXP/N', 'USB3 SS TX (combo PHY2)', 'USB3 PHY', 'LTE modem USB 3.0 TX', 'M.2 pins 37/35 (USB_SS_RX_P/M) via 100 nF', 'decision Q7; host-side AC caps per Quectel Fig. 18', 'PX J1; EM060K HD V1.1 Fig. 18')
add('C', '57,59', 'USB30_2_SSRXP/N', 'USB3 SS RX (combo PHY2)', 'USB3 PHY', 'LTE modem USB 3.0 RX', 'M.2 pins 31/29 (USB_SS_TX_P/M), no caps (inside module)', 'combo PHY2 set to USB3 mode in device tree', 'PX J1; EM060K HD V1.1 Fig. 18')
add('C', '89', 'GPIO4_A6', 'GPIO4_A6', 'VCCIO6 3.3 V', 'Hub reset', 'USB2514B RESET_N (+ RC)', '', 'PX J1; CM5 p17')
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add('B', '187,189', 'MIPI_DPHY1_TX_CLKN/P', 'DSI1 clock', 'MIPI D-PHY', 'Display clock lane', 'Panel FPC pins 13/14', '', 'PX U13-B')
add('A', '41', 'LCD_RESET_L', 'GPIO1_B0', 'VCCIO4 1.8 V', 'Panel reset', 'Panel RESET (26); panel IOVCC is 1.8 V', 'no translator needed', 'PX; panel DS s.4.1, 6.2')
add('C', '34', 'LCD_PWREN_H', 'GPIO4_A3', 'VCCIO6 3.3 V', 'Panel power enable', 'Load switch for panel VCI 3.3 V', '', 'PX J1')
add('A', '21', 'PWM15_M1', 'GPIO4_B3', 'VCCIO6 3.3 V', 'Backlight PWM / enable', 'TPS61169 CTRL', '', 'PX; IO p10')
add('C', '69', 'I2C6_SDA_M3', 'GPIO4_B0', 'VCCIO6 3.3 V', 'Touch + keyboard I2C SDA', 'GT911 SDA (CTP FPC pin 5); keyboard FFC pin 8 (RP2040 I2C target 0x1F)', 'GT911 logic is 3.3 V; free because there is no FUSB302', 'PX J1; panel DS s.1.2, 4.2')
add('C', '71', 'I2C6_SCL_M3', 'GPIO4_B1', 'VCCIO6 3.3 V', 'Touch + keyboard I2C SCL', 'GT911 SCL (CTP pin 4); keyboard FFC pin 9', '', 'PX J1')
add('C', '38', 'GPIO4_A4', 'GPIO4_A4', 'VCCIO6 3.3 V', 'Touch INT', 'GT911 INT (pin 6)', 'bidirectional: also selects GT911 I2C address at reset', 'PX J1')
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add('A', '48', 'I2S0_LRCK_TX', 'GPIO1_C5', 'VCCIO1 1.8 V', 'I2S LRCLK', 'MAX98357A x2 LRCLK', '', 'PX; CM5 p13')
add('A', '34', 'I2S0_SDO0', 'GPIO1_C7', 'VCCIO1 1.8 V', 'I2S data', 'MAX98357A x2 DIN', '', 'PX; CM5 p13')
add('C', '98', 'BT_REG_ON_H', 'GPIO0_D4', 'PMUIO2 3.3 V', 'Amp enable / channel select', 'MAX98357A SD_MODE: left amp via ~2k, right amp via 210k (Table 6)', '', 'PX J1; MAX98357A DS Table 5/6')
add('C', '75', 'GPIO1_C6_S', 'PDM0_CLK0_M0', 'VCCIO1 1.8 V', 'PDM mic clock', 'MEMS PDM microphone CLK', '', 'PX J1 func list')
add('C', '77', 'GPIO1_D5_S', 'PDM0_SDI0_M0', 'VCCIO1 1.8 V', 'PDM mic data', 'MEMS PDM microphone DATA', '', 'PX J1 func list')

add('C', '18', 'PWM11_M3', 'GPIO3_D5', 'VCCIO5 3.3 V', 'Charger PROCHOT# (throttle request)', 'BQ25713 PROCHOT# (open drain, 10k pull-up to VCC_3V3_S3)', 'asserts on battery-discharge current, low VSYS, input over-current: Linux throttles CPU/GPU', 'PX J1; BQ25713 DS pin 11')

# ---------------- Keyboard board interface ----------------
add('C', '93', 'GPIO0_C2', 'GPIO0_C2', 'PMUIO2 3.3 V', '5 V rail enable', 'TPS61089 EN (100k pull-up to VCC_3V3_S3 = on by default)', 'lets software drop USB-A/keyboard power in suspend', 'PX J1; CM5 p9')
add('C', '95', 'TYPEC5V_PWREN_H', 'GPIO0_D5', 'PMUIO2 3.3 V', 'Keyboard INT# (wake)', 'FFC pin 10 (10k pull-up to 3V3_S3, 1k series)', 'PMU GPIO so a key press can wake the SoC', 'PX J1; CM5 p9')
add('C', '87', 'GPIO4_A7', 'GPIO4_A7', 'VCCIO6 3.3 V', 'Keyboard RESET#', 'FFC pin 11 -> RP2040 RUN (open drain)', '', 'PX J1')
add('C', '85', 'BT_HOST_WAKE', 'GPIO4_B5', 'VCCIO6 3.3 V', 'Keyboard BOOT#', 'FFC pin 12 -> RP2040 QSPI_SS via 1k (open drain)', 'Radxa net name is BT_HOST_WAKE; repurposed', 'PX J1')

# ---------------- Deliberately unconnected (notable) ----------------
NC = [
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

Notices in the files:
gen/build_b.py:
Derived from Solder Party BBQ20KBD (CERN-OHL v1.2): same RP2040 GPIO map, so the i2c_puppet firmware
